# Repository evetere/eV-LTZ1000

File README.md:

# eV-LTZ1000
LTZ1000 reference schematic and board (kicad)

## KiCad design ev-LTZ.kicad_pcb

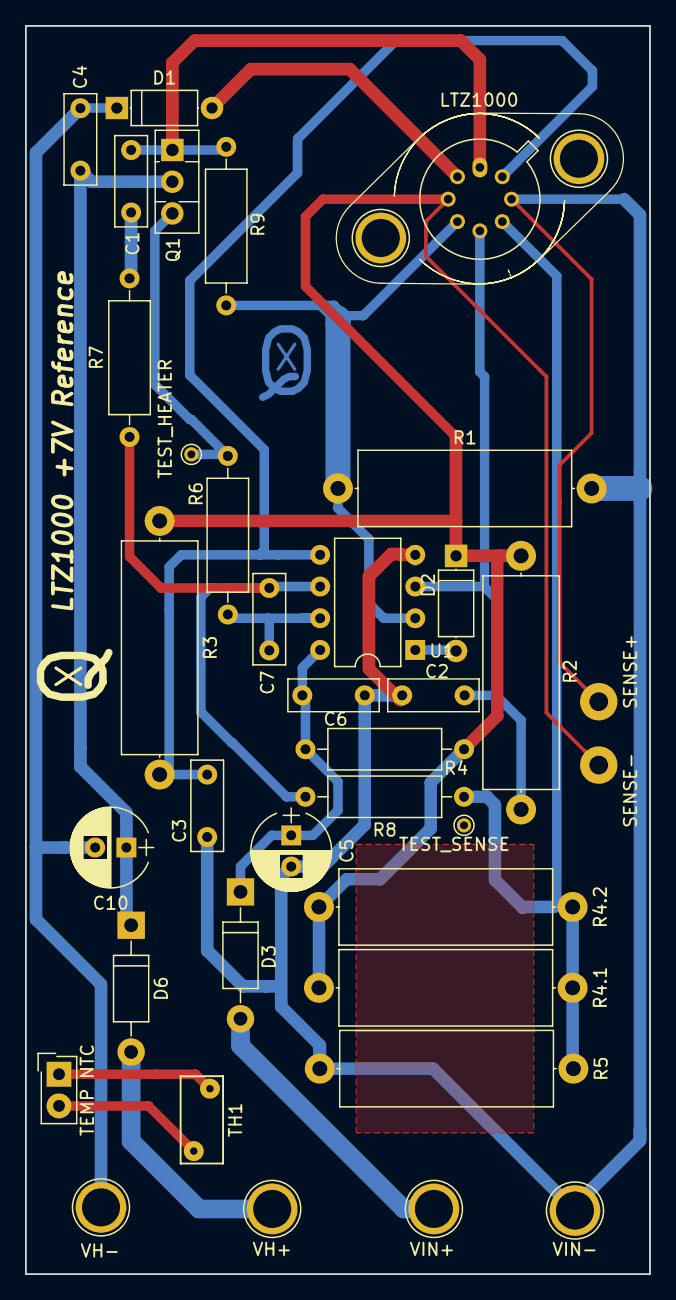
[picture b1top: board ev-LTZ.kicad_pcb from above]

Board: 2 copper layers, 50.0 x 100.0 mm, 36 parts (0 on the bottom side), 20 nets.

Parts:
C1, C3, C4, C6: .1uF; C_Rect_L7.2mm_W2.5mm_P5.00mm_FKS2_FKP2_MKS2_MKP2
C2, C7: 0.022uF; C_Rect_L7.2mm_W2.5mm_P5.00mm_FKS2_FKP2_MKS2_MKP2
C5, C10: 47uF; CP_Radial_D6.3mm_P2.50mm
D1, D2: 1N4148; D_A-405_P7.62mm_Horizontal
D3, D6: 1N5819; D_DO-41_SOD81_P10.16mm_Horizontal
LTZ1000-1: LTZ1000; TO-5-8_PD5.08
P1: VIN+; 1pin
P2: TEMP NTC; SL-102-X-XX_1x02
P3: VH-; 1pin
P4: VH+; 1pin
P5: SENSE-; Measurement_Point_Round-TH_Big
P6: SENSE+; Measurement_Point_Round-TH_Big
P7: VIN-; 1pin
Q1: BD139; TO-126_Vertical
R1: 120; R_Axial_DIN0617_L17.0mm_D6.0mm_P20.32mm_Horizontal
R2, R3: 70k; R_Axial_DIN0617_L17.0mm_D6.0mm_P20.32mm_Horizontal
R4: 100k; R_Axial_DIN0309_L9.0mm_D3.2mm_P12.70mm_Horizontal
R4.1, R4.2: 25k; R_Axial_DIN0617_L17.0mm_D6.0mm_P20.32mm_Horizontal
R5: 1k; R_Axial_DIN0617_L17.0mm_D6.0mm_P20.32mm_Horizontal
R6: 1k; R_Axial_DIN0309_L9.0mm_D3.2mm_P12.70mm_Horizontal
R7: 1M; R_Axial_DIN0309_L9.0mm_D3.2mm_P12.70mm_Horizontal
R8: 10k; R_Axial_DIN0309_L9.0mm_D3.2mm_P12.70mm_Horizontal
R9: 400k; R_Axial_DIN0309_L9.0mm_D3.2mm_P12.70mm_Horizontal
TH1: 10k; RV_Disc_D7_W3.4_P5
U1: LT1013N8; DIP-8_W7.62mm
W1: TEST_HEATER; PINTST
W2: TEST_SENSE; PINTST

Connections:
/CURRENT_OUT: D2.2, U1.1
/HEAT: Q1.3, R6.2, W1.1
/HEATER+: C1.2, LTZ1000-1.1, Q1.1, R9.2
/HEATER-: D1.2, LTZ1000-1.2
/SENSE+: D2.1, LTZ1000-1.3, P6.1, R2.1, R3.1, R4.1, R4.1.1, R4.2.1
/TCOMP: C2.1, LTZ1000-1.5, R2.2, U1.3
/TSENSE_B: LTZ1000-1.6, R4.1.2, R4.2.2, R5.1, R8.1, W2.1
/TSENSE_C: C3.1, LTZ1000-1.8, R3.2, U1.5
/VCCH: C4.1, C10.1, D6.1, Q1.2
/VCCOPAMP: C5.1, C6.1, D3.1, R4.2, U1.8
/VH+: D6.2, P4.1
/VH-: C4.2, C10.2, D1.1, P3.1
/VIN+: D3.2, P1.1
/ZENER-: LTZ1000-1.4, R1.1, R9.1, U1.2
GND: C2.2, C3.2, C5.2, C6.2, LTZ1000-1.7, P5.1, P7.1, R1.2, R5.2, U1.4
unnamed: C1.1, R7.2
unnamed: C7.1, R7.1, R8.2, U1.6
unnamed: C7.2, R6.1, U1.7
unnamed: P2.1, TH1.2
unnamed: P2.2, TH1.1

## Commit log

2017-09-15 rename
2017-09-28 unify projects
2017-09-28 new ltz lib
2017-09-28 TiN comments
2017-09-28 fix TiN comments
2017-09-28 guard ring
2017-09-28 bump
2017-11-08 V00 of pcb
2017-11-09 finish pcb
2017-11-28 change footprint
2017-11-29 modify layout
2017-12-01 improve traces
2017-12-17 change layout
